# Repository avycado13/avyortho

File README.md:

# AvyOrtho
A basic 40% ortholinear keyboard that uses vim keys for arrows

I wanted to make a nice keyboard and I wanted one that could be small and easy to carry in my backpack. I decided on an ortholinear because I figured they would be a lot easier to build and route because the keys aren't spaced weirdly. I decided to use ZMK for my firmware because there are nice tools to let you export your JSON from keyboard layout editor and turn it into firmware for ZMK. I used a Seeed Studios XIAO nRF52840 Plus for the microcontroller because it had enough GPIO pins and because it could do batteries without external devices needed

I chose to go with a minimal 4x12 setup so I could fit it in my bag and to make it cooler. I will probably do keys like function keys with a layer and a modifier key for other functionality. In my next keyboard, I might consider adding RGB lights with something like a sk6812-mini. I will probably mainly use this keyboard on the go and then build a bigger keyboard as my home keyboard.

## Firmware
I used ZMK and made the config using [ZMK Shield Wizard](https://shield-wizard.genteure.com/). It is built with GitHub Actions on every commit.

## Bill of Materials

PCB components (designators and footprints in [`production/bom.csv`](production/bom.csv)). Prices below are USD snapshots from the selected offers in [`ordering/`](ordering/), **not live quotes**; check price, stock, shipping, and tax before ordering.

| Part | Qty on PCB | Order qty | Part / supplier link | Unit price | Order cost |
|------|-----------:|----------:|----------------------|-----------:|-----------:|
| 1N4148W SMD diodes (D1–D48, except D44) | 47 | 50 | [LCSC C241939](https://lcsc.com/product-detail/C241939.html) | $0.037 | $1.85 |
| 806 kΩ 0805 resistor (R1) | 1 | 1 | [Vishay CRCW0805806KFKEA — Mouser 71-CRCW0805-806K-E3](https://www.mouser.com/ProductDetail/71-CRCW0805-806K-E3) | $0.10 | $0.10 |
| 2 MΩ 0805 resistor (R2) | 1 | 1 | [TE CPF0805B2M0E — Mouser 279-CPF0805B2M0E](https://www.mouser.com/ProductDetail/279-CPF0805B2M0E) | $0.25 | $0.25 |
| Kailh MX hotswap sockets (SW1–SW48, except SW44) | 47 | 3 × 20-pack | [Adafruit 4958](https://www.adafruit.com/product/4958) ([Mouser 485-4958](https://www.mouser.com/ProductDetail/485-4958)) | $4.95 / pack | $14.85 |
| Seeed XIAO nRF52840 Plus (U3) | 1 | 1 | [Mouser 713-102010672](https://www.mouser.com/ProductDetail/713-102010672) | $10.40 | $10.40 |
| **PCB component total** | | | | | **$27.45** |

R2's selected offer is an alternative to the BOM's CRCW08052M00FKED (same 2 MΩ value and 0805 size); confirm specifications before substituting. The sockets are priced per **20-pack**, not individually. The total excludes shipping, tax, PCB fabrication, and the following build-dependent items (no specific product or price selected):

- 47 × MX-compatible switches — choose a compatible switch and check its current price.
- 47 × 1u MX-compatible keycaps — choose a set and check its current price.
- Case and plate — see the [case CAD](cad/body.step) and [plate CAD](cad/plate.step) for fabrication; cost depends on material and manufacturer.

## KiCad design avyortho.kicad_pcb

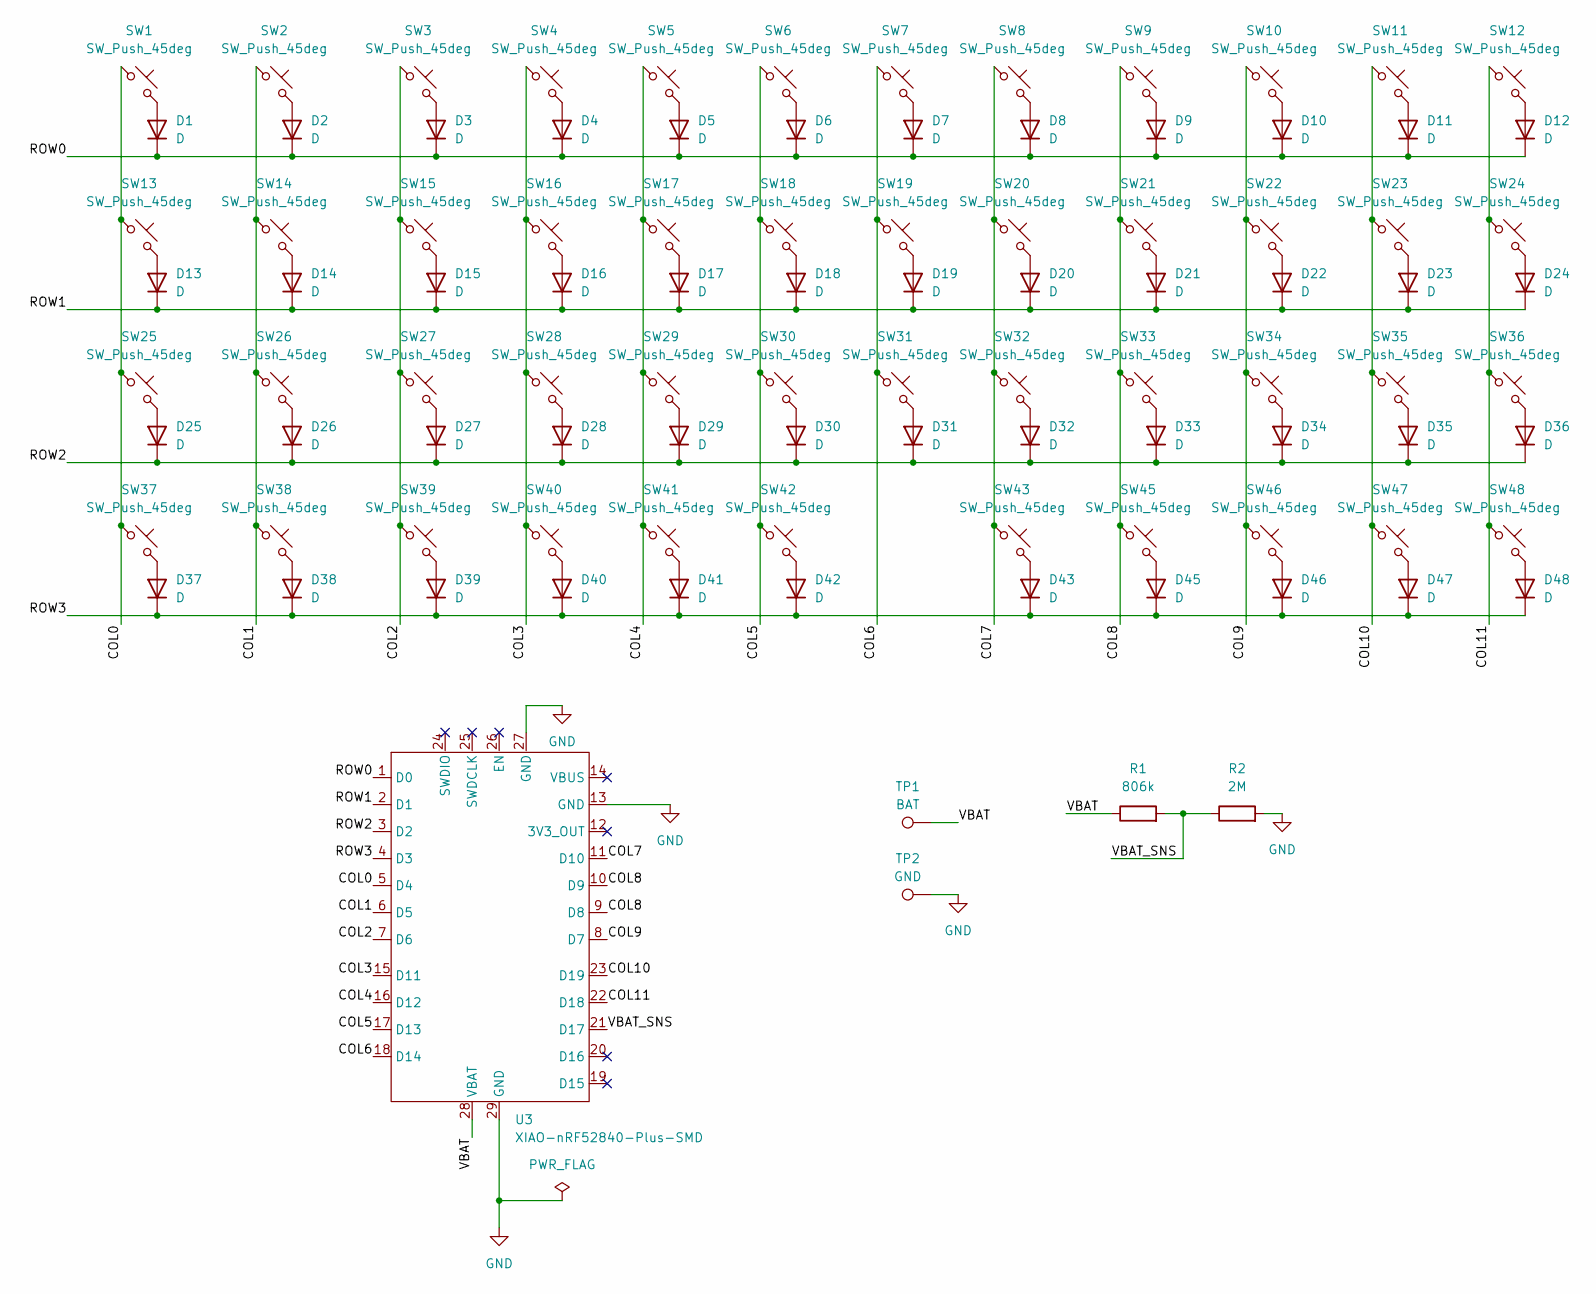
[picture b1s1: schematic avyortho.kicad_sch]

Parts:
D1, D2, D3, D4, D5, D6, D7, D8, D9, D10, D11, D12, D13, D14, D15, D16, D17, D18, D19, D20, D21, D22, D23, D24, D25, D26, D27, D28, D29, D30, D31, D32, D33, D34, D35, D36, D37, D38, D39, D40, D41, D42, D43, D45, D46, D47, D48: D; D_SOD-123; MPN 1N4148W
R1: 806k; R_0805_2012Metric_Pad1.20x1.40mm_HandSolder; MPN CRCW0805806KFKEA
R2: 2M; R_0805_2012Metric_Pad1.20x1.40mm_HandSolder; MPN CRCW08052M00FKED
SW1, SW2, SW3, SW4, SW5, SW6, SW7, SW8, SW9, SW10, SW11, SW12, SW13, SW14, SW15, SW16, SW17, SW18, SW19, SW20, SW21, SW22, SW23, SW24, SW25, SW26, SW27, SW28, SW29, SW30, SW31, SW32, SW33, SW34, SW35, SW36, SW37, SW38, SW39, SW40, SW41, SW42, SW43, SW45, SW46, SW47, SW48: SW_Push_45deg; SW_MX_HS_CPG151101S11_1u; MPN CPG151101S11-16
TP1: BAT; TestPoint_Pad_D3.0mm
TP2: GND; TestPoint_Pad_D3.0mm
U3: XIAO-nRF52840-Plus-SMD; MPN 102010672

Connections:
/COL0: SW1.1, SW13.1, SW25.1, SW37.1, U3.5 (D4)
/COL1: SW2.1, SW14.1, SW26.1, SW38.1, U3.6 (D5)
/COL2: SW3.1, SW15.1, SW27.1, SW39.1, U3.7 (D6)
/COL3: SW4.1, SW16.1, SW28.1, SW40.1, U3.15 (D11)
/COL4: SW5.1, SW17.1, SW29.1, SW41.1, U3.16 (D12)
/COL5: SW6.1, SW18.1, SW30.1, SW42.1, U3.17 (D13)
/COL6: SW7.1, SW19.1, SW31.1, U3.18 (D14)
/COL7: SW8.1, SW20.1, SW32.1, SW43.1, U3.11 (D10)
/COL8: SW9.1, SW21.1, SW33.1, SW45.1, U3.9 (D8), U3.10 (D9)
/COL9: SW10.1, SW22.1, SW34.1, SW46.1, U3.8 (D7)
/COL10: SW11.1, SW23.1, SW35.1, SW47.1, U3.23 (D19)
/COL11: SW12.1, SW24.1, SW36.1, SW48.1, U3.22 (D18)
/ROW0: D1.1 (K), D2.1 (K), D3.1 (K), D4.1 (K), D5.1 (K), D6.1 (K), D7.1 (K), D8.1 (K), D9.1 (K), D10.1 (K), D11.1 (K), D12.1 (K), U3.1 (D0)
/ROW1: D13.1 (K), D14.1 (K), D15.1 (K), D16.1 (K), D17.1 (K), D18.1 (K), D19.1 (K), D20.1 (K), D21.1 (K), D22.1 (K), D23.1 (K), D24.1 (K), U3.2 (D1)
/ROW2: D25.1 (K), D26.1 (K), D27.1 (K), D28.1 (K), D29.1 (K), D30.1 (K), D31.1 (K), D32.1 (K), D33.1 (K), D34.1 (K), D35.1 (K), D36.1 (K), U3.3 (D2)
/ROW3: D37.1 (K), D38.1 (K), D39.1 (K), D40.1 (K), D41.1 (K), D42.1 (K), D43.1 (K), D45.1 (K), D46.1 (K), D47.1 (K), D48.1 (K), U3.4 (D3)
/VBAT: R1.1, TP1.1 (1_1), U3.28 (VBAT)
/VBAT_SNS: R1.2, R2.1, U3.21 (D17)
GND: R2.2, TP2.1 (1_1), U3.13 (GND), U3.27 (GND), U3.29 (GND)
unnamed: D1.2 (A), SW1.2
unnamed: D2.2 (A), SW2.2
unnamed: D3.2 (A), SW3.2
unnamed: D4.2 (A), SW4.2
unnamed: D5.2 (A), SW5.2
unnamed: D6.2 (A), SW6.2
unnamed: D7.2 (A), SW7.2
unnamed: D8.2 (A), SW8.2
unnamed: D9.2 (A), SW9.2
unnamed: D10.2 (A), SW10.2
unnamed: D11.2 (A), SW11.2
unnamed: D12.2 (A), SW12.2
unnamed: D13.2 (A), SW13.2
unnamed: D14.2 (A), SW14.2
unnamed: D15.2 (A), SW15.2
unnamed: D16.2 (A), SW16.2
unnamed: D17.2 (A), SW17.2
unnamed: D18.2 (A), SW18.2
unnamed: D19.2 (A), SW19.2
unnamed: D20.2 (A), SW20.2
unnamed: D21.2 (A), SW21.2
unnamed: D22.2 (A), SW22.2
unnamed: D23.2 (A), SW23.2
unnamed: D24.2 (A), SW24.2
unnamed: D25.2 (A), SW25.2
unnamed: D26.2 (A), SW26.2
unnamed: D27.2 (A), SW27.2
unnamed: D28.2 (A), SW28.2
unnamed: D29.2 (A), SW29.2
unnamed: D30.2 (A), SW30.2
unnamed: D31.2 (A), SW31.2
unnamed: D32.2 (A), SW32.2
unnamed: D33.2 (A), SW33.2
unnamed: D34.2 (A), SW34.2
unnamed: D35.2 (A), SW35.2
unnamed: D36.2 (A), SW36.2
unnamed: D37.2 (A), SW37.2
unnamed: D38.2 (A), SW38.2
unnamed: D39.2 (A), SW39.2
unnamed: D40.2 (A), SW40.2
unnamed: D41.2 (A), SW41.2
unnamed: D42.2 (A), SW42.2
unnamed: D43.2 (A), SW43.2
unnamed: D45.2 (A), SW45.2
unnamed: D46.2 (A), SW46.2
unnamed: D47.2 (A), SW47.2
unnamed: D48.2 (A), SW48.2

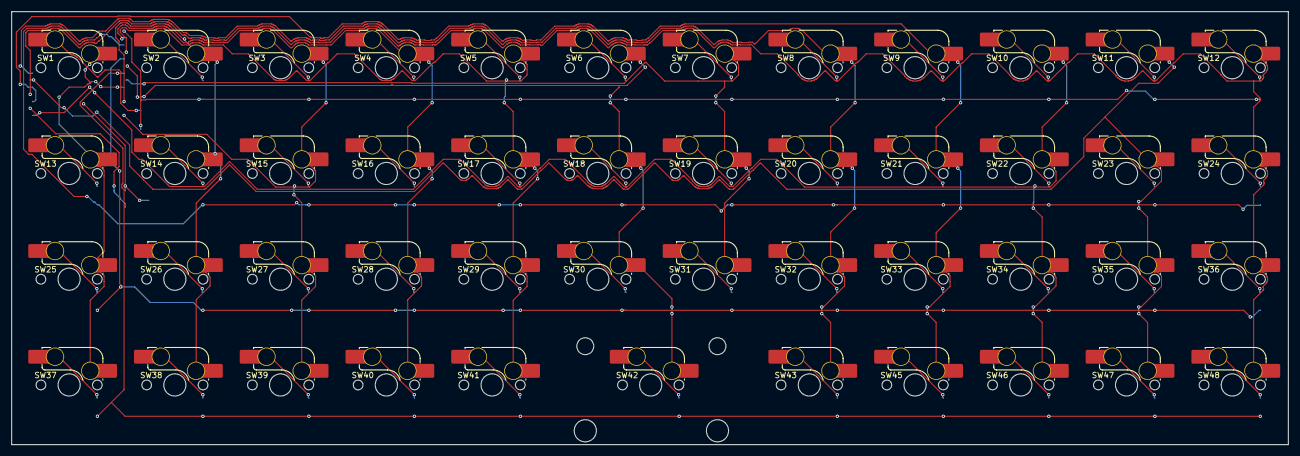
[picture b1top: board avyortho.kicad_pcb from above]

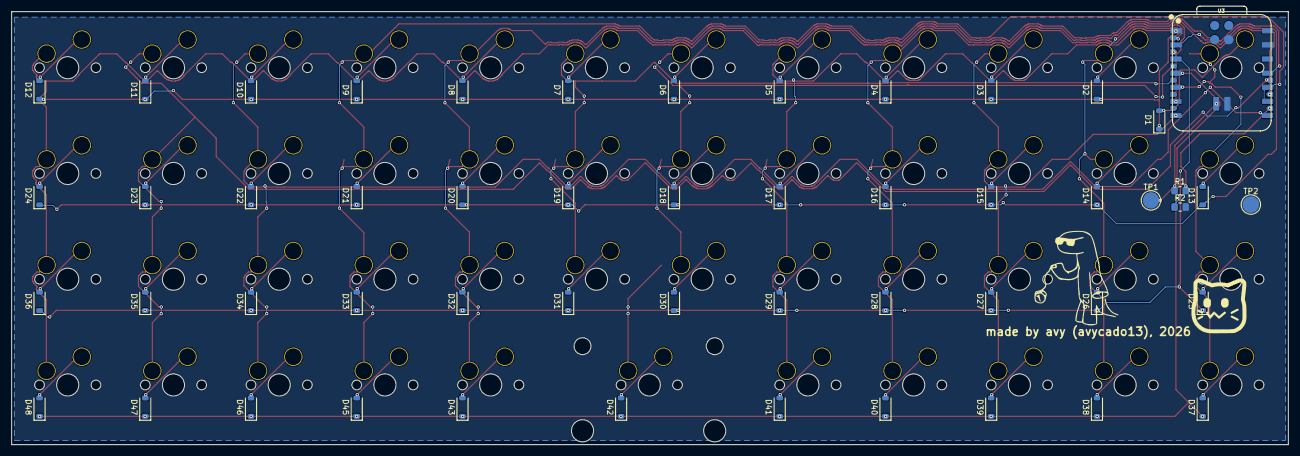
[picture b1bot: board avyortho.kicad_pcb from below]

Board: 2 copper layers, 230.0 x 78.0 mm, 99 parts (52 on the bottom side), 66 nets.

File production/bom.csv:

Designator,Footprint,Quantity,Value,LCSC Part #
"D1, D10, D11, D12, D13, D14, D15, D16, D17, D18, D19, D2, D20, D21, D22, D23, D24, D25, D26, D27, D28, D29, D3, D30, D31, D32, D33, D34, D35, D36, D37, D38, D39, D4, D40, D41, D42, D43, D45, D46, D47, D48, D5, D6, D7, D8, D9",D_SOD-123,47,D,1N4148W
R1,0805,1,806k,CRCW0805806KFKEA
R2,0805,1,2M,CRCW08052M00FKED
"SW1, SW10, SW11, SW12, SW13, SW14, SW15, SW16, SW17, SW18, SW19, SW2, SW20, SW21, SW22, SW23, SW24, SW25, SW26, SW27, SW28, SW29, SW3, SW30, SW31, SW32, SW33, SW34, SW35, SW36, SW37, SW38, SW39, SW4, SW40, SW41, SW42, SW43, SW45, SW46, SW47, SW48, SW5, SW6, SW7, SW8, SW9",SW_MX_HS_CPG151101S11_1u,47,SW_Push_45deg,CPG151101S11-16
U3,XIAO-nRF52840-Plus-SMD,1,XIAO-nRF52840-Plus-SMD,102010672
